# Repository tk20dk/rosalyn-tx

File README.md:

# rosalyn-tx
LoRa TX module for TURNIGY 9x

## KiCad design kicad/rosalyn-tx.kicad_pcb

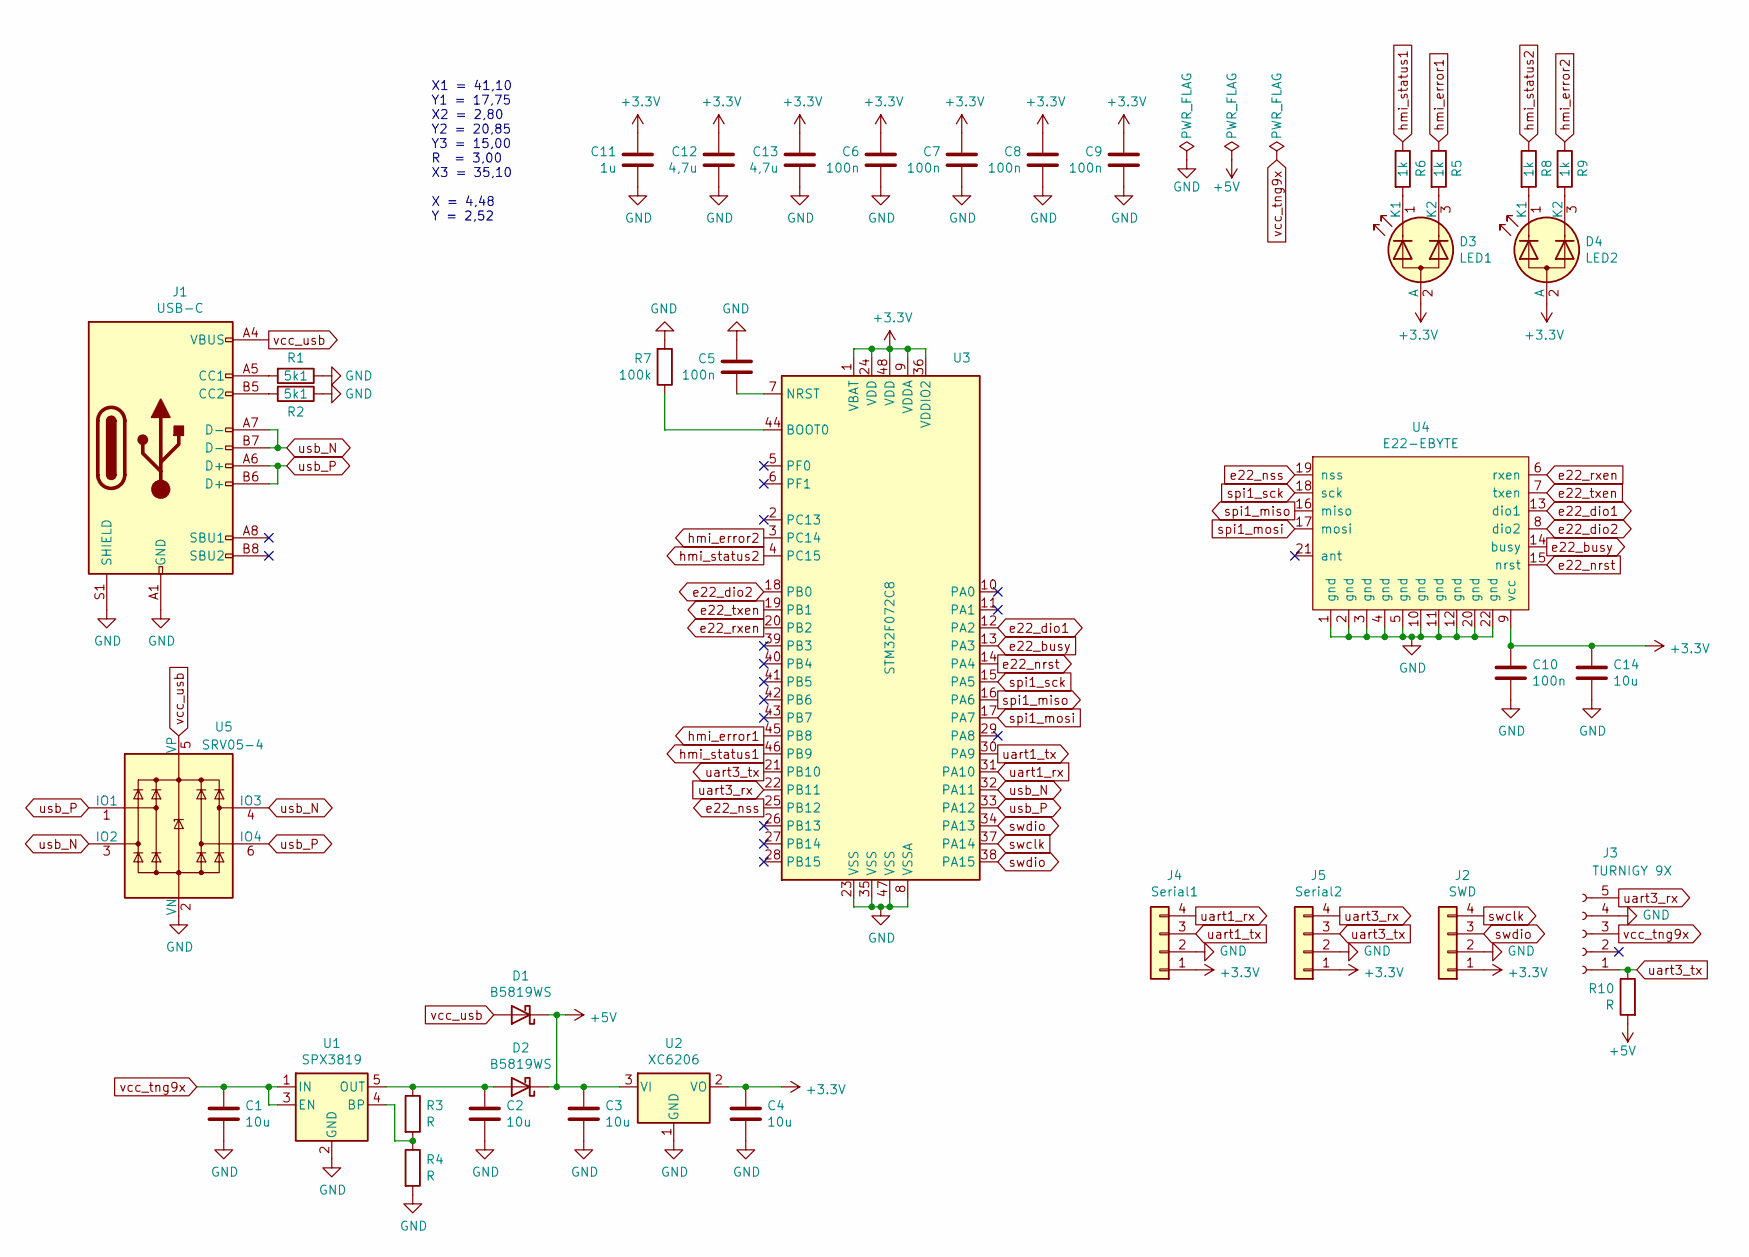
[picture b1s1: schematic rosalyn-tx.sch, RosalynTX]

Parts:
C1, C2, C14: 10u; C_0805_2012Metric
C3, C4: 10u; C_1206_3216Metric
C5, C6, C7, C8, C9, C10: 100n; C_0603_1608Metric
C11: 1u; C_0603_1608Metric
C12, C13: 4,7u; C_0603_1608Metric
D1, D2: B5819WS; D_SOD-323
D3: LED1; LED_D3.0mm-3
D4: LED2; LED_D3.0mm-3
J1: USB-C; usb-c_14pin_tht_vertical
J2: SWD; JST_SH_BM04B-SRSS-TB_1x04-1MP_P1.00mm_Vertical
J3: TURNIGY 9X; PinSocket_1x05_P2.54mm_Vertical
J4: Serial1; JST_SH_BM04B-SRSS-TB_1x04-1MP_P1.00mm_Vertical
J5: Serial2; JST_SH_BM04B-SRSS-TB_1x04-1MP_P1.00mm_Vertical
R1, R2: 5k1; R_0603_1608Metric
R3, R4, R10: R; R_0603_1608Metric
R5, R6, R8, R9: 1k; R_0603_1608Metric
R7: 100k; R_0603_1608Metric
U1: SPX3819; SOT-23-5
U2: XC6206; SOT-23
U3: STM32F072C8; LQFP-48_7x7mm_P0.5mm
U4: E22-EBYTE
U5: SRV05-4; SOT-23-6

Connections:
+3V3: C4.1, C6.2, C7.2, C8.2, C9.2, C10.1, C11.2, C12.2, C13.2, C14.1, D3.2 (A), D4.2 (A), J2.1, J4.1, J5.1, U2.2 (VO), U3.1 (VBAT), U3.9 (VDDA), U3.24 (VDD), U3.36 (VDDIO2), U3.48 (VDD), U4.9 (vcc)
+5V: C3.1, D1.1 (K), D2.1 (K), R10.2, U2.3 (VI)
unnamed: C2.1, D2.2 (A), R3.1, U1.5 (OUT)
unnamed: C5.1, U3.7 (NRST)
unnamed: D3.1 (K1), R6.2
unnamed: D3.3 (K2), R5.2
unnamed: D4.1 (K1), R8.2
unnamed: D4.3 (K2), R9.2
unnamed: J1.A5 (CC1), R1.2
unnamed: J1.B5 (CC2), R2.2
unnamed: R3.2, R4.1, U1.4 (BP)
unnamed: R7.1, U3.44 (BOOT0)
hmi_error: R5.1, U3.45 (PB8)
hmi_error_ext: R9.1, U3.3 (PC14)
hmi_status: R6.1, U3.46 (PB9)
hmi_status_ext: R8.1, U3.4 (PC15)
radio_busy: U3.13 (PA3), U4.14 (busy)
radio_dio1: U3.12 (PA2), U4.13 (dio1)
radio_dio2: U3.18 (PB0), U4.8 (dio2)
radio_nrst: U3.14 (PA4), U4.15 (nrst)
radio_nss: U3.25 (PB12), U4.19 (nss)
radio_rxen: U3.20 (PB2), U4.6 (rxen)
radio_txen: U3.19 (PB1), U4.7 (txen)
spi1_miso: U3.16 (PA6), U4.16 (miso)
spi1_mosi: U3.17 (PA7), U4.17 (mosi)
spi1_sck: U3.15 (PA5), U4.18 (sck)
swclk: J2.4, U3.37 (PA14)
swdio: J2.3, U3.34 (PA13), U3.38 (PA15)
uart1_rx: J4.4, U3.31 (PA10)
uart1_tx: J4.3, U3.30 (PA9)
uart3_rx: J3.5, J5.4, U3.22 (PB11)
uart3_tx: J3.1, J5.3, R10.1, U3.21 (PB10)
usb_N: J1.A7 (D-), J1.B7 (D-), U3.32 (PA11), U5.3 (IO2), U5.4 (IO3)
usb_P: J1.A6 (D+), J1.B6 (D+), U3.33 (PA12), U5.1 (IO1), U5.6 (IO4)
vcc_tng9x: C1.1, J3.3, U1.1 (IN), U1.3 (EN)
vcc_usb: D1.2 (A), J1.A4 (VBUS), J1.A9 (VBUS), J1.B4 (VBUS), J1.B9 (VBUS), U5.5 (VP)

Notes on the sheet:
X1 = 41,10 Y1 = 17,75 X2 = 2,80 Y2 = 20,85 Y3 = 15,00 R = 3,00 X3 = 35,10 X = 4,48 Y = 2,52

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
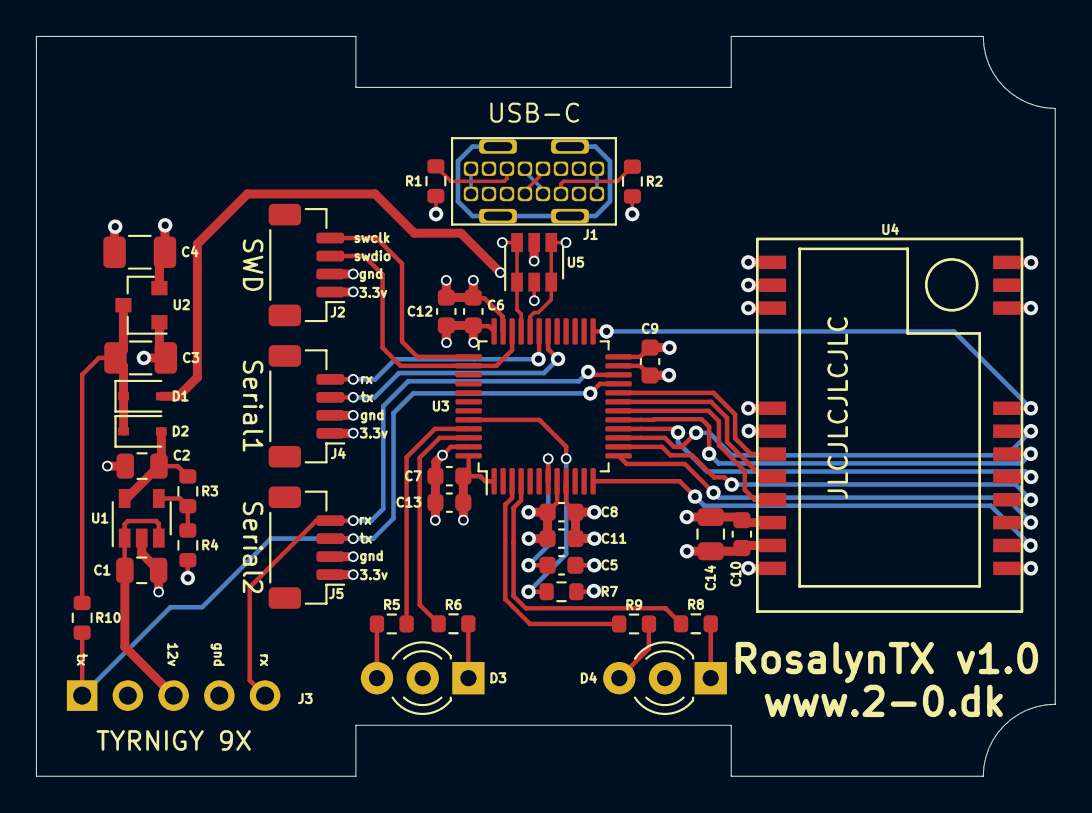
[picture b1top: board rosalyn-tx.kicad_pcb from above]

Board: 4 copper layers, 56.6 x 41.1 mm, 38 parts (1 on the bottom side), 37 nets.

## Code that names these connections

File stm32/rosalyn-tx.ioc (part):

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Mcu.Name=STM32F072C(8-B)Tx
Mcu.Package=LQFP48
Mcu.UserName=STM32F072C8Tx
PA10.GPIOParameters=GPIO_PuPd
PA10.GPIO_PuPd=GPIO_PULLUP
PA10.Mode=Asynchronous
PA10.Signal=USART1_RX
PA11.Mode=Device
PA11.Signal=USB_DM
PA12.Mode=Device
PA12.Signal=USB_DP
PA13.Mode=Serial_Wire
PA13.Signal=SYS_SWDIO
PA14.Mode=Serial_Wire
PA14.Signal=SYS_SWCLK
PA2.GPIOParameters=GPIO_Label
PA2.GPIO_Label=RADIO_DIO1
PA2.Signal=GPXTI2
PA3.GPIOParameters=GPIO_Label
PA3.GPIO_Label=RADIO_BUSY
PA3.Signal=GPIO_Input
PA4.GPIOParameters=PinState,GPIO_Label
PA4.GPIO_Label=RADIO_NRST
PA4.PinState=GPIO_PIN_SET
PA4.Signal=GPIO_Output
PA5.Mode=Full_Duplex_Master
PA5.Signal=SPI1_SCK
PA6.GPIOParameters=GPIO_PuPd
PA6.GPIO_PuPd=GPIO_PULLUP
PA6.Mode=Full_Duplex_Master
PA6.Signal=SPI1_MISO
PA7.Mode=Full_Duplex_Master
PA7.Signal=SPI1_MOSI
PA9.Mode=Asynchronous
PA9.Signal=USART1_TX
PB0.GPIOParameters=GPIO_Label
PB0.GPIO_Label=RADIO_DIO2
PB0.Signal=GPIO_Input
PB1.GPIOParameters=GPIO_Label
PB1.GPIO_Label=RADIO_TXEN
PB1.Signal=GPIO_Output
PB11.GPIOParameters=GPIO_ModeDefaultPP
PB11.GPIO_ModeDefaultPP=GPIO_MODE_AF_PP
PB11.Signal=S_TIM2_CH4
PB12.GPIOParameters=PinState,GPIO_Label
PB12.GPIO_Label=RADIO_NSS
PB12.PinState=GPIO_PIN_SET
PB12.Signal=GPIO_Output
PB2.GPIOParameters=GPIO_Label
PB2.GPIO_Label=RADIO_RXEN
PB2.Signal=GPIO_Output
PB8.GPIOParameters=PinState,GPIO_Label
PB8.GPIO_Label=HMI_ERROR
PB8.PinState=GPIO_PIN_SET
PB8.Signal=GPIO_Output
PB9.GPIOParameters=PinState,GPIO_Label
PB9.GPIO_Label=HMI_STATUS
PB9.PinState=GPIO_PIN_SET
PB9.Signal=GPIO_Output
PC14-OSC32_IN.GPIOParameters=PinState,GPIO_Label
PC14-OSC32_IN.GPIO_Label=HMI_ERROR_EXT
PC14-OSC32_IN.PinState=GPIO_PIN_SET
PC14-OSC32_IN.Signal=GPIO_Output
PC15-OSC32_OUT.GPIOParameters=PinState,GPIO_Label
PC15-OSC32_OUT.GPIO_Label=HMI_STATUS_EXT
PC15-OSC32_OUT.PinState=GPIO_PIN_SET
PC15-OSC32_OUT.Signal=GPIO_Output
RCC.SYSCLKFreq_VALUE=48000000
RCC.SYSCLKSource=RCC_SYSCLKSOURCE_HSI48
board=custom

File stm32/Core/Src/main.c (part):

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
  LL_AHB1_GRP1_EnableClock(LL_AHB1_GRP1_PERIPH_GPIOA);
  /**USART1 GPIO Configuration
  PA9   ------> USART1_TX
  PA10   ------> USART1_RX
  */
  GPIO_InitStruct.Pin = LL_GPIO_PIN_9;
  GPIO_InitStruct.Mode = LL_GPIO_MODE_ALTERNATE;
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  __HAL_RCC_GPIOB_CLK_ENABLE();

  /*Configure GPIO pin Output Level */
  HAL_GPIO_WritePin(GPIOC, HMI_ERROR_EXT_Pin|HMI_STATUS_EXT_Pin, GPIO_PIN_SET);

  /*Configure GPIO pin Output Level */
  HAL_GPIO_WritePin(RADIO_NRST_GPIO_Port, RADIO_NRST_Pin, GPIO_PIN_SET);

  /*Configure GPIO pin Output Level */
  HAL_GPIO_WritePin(GPIOB, RADIO_TXEN_Pin|RADIO_RXEN_Pin, GPIO_PIN_RESET);

  /*Configure GPIO pin Output Level */
  HAL_GPIO_WritePin(GPIOB, RADIO_NSS_Pin|HMI_ERROR_Pin|HMI_STATUS_Pin, GPIO_PIN_SET);

  /*Configure GPIO pin : PC13 */
  GPIO_InitStruct.Pin = GPIO_PIN_13;
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  GPIO_InitStruct.Pull = GPIO_NOPULL;
  HAL_GPIO_Init(GPIOC, &GPIO_InitStruct);

  /*Configure GPIO pins : HMI_ERROR_EXT_Pin HMI_STATUS_EXT_Pin */
  GPIO_InitStruct.Pin = HMI_ERROR_EXT_Pin|HMI_STATUS_EXT_Pin;
  GPIO_InitStruct.Mode = GPIO_MODE_OUTPUT_PP;
  GPIO_InitStruct.Pull = GPIO_NOPULL;
  GPIO_InitStruct.Speed = GPIO_SPEED_FREQ_LOW;
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  GPIO_InitStruct.Pull = GPIO_NOPULL;
  HAL_GPIO_Init(GPIOF, &GPIO_InitStruct);

  /*Configure GPIO pins : PA0 PA1 PA8 PA15 */
  GPIO_InitStruct.Pin = GPIO_PIN_0|GPIO_PIN_1|GPIO_PIN_8|GPIO_PIN_15;
  GPIO_InitStruct.Mode = GPIO_MODE_ANALOG;
  GPIO_InitStruct.Pull = GPIO_NOPULL;
  HAL_GPIO_Init(GPIOA, &GPIO_InitStruct);

  /*Configure GPIO pin : RADIO_DIO1_Pin */
  GPIO_InitStruct.Pin = RADIO_DIO1_Pin;
  GPIO_InitStruct.Mode = GPIO_MODE_IT_RISING;
  GPIO_InitStruct.Pull = GPIO_NOPULL;
  HAL_GPIO_Init(RADIO_DIO1_GPIO_Port, &GPIO_InitStruct);

  /*Configure GPIO pin : RADIO_BUSY_Pin */
  GPIO_InitStruct.Pin = RADIO_BUSY_Pin;
  GPIO_InitStruct.Mode = GPIO_MODE_INPUT;
  GPIO_InitStruct.Pull = GPIO_NOPULL;
  HAL_GPIO_Init(RADIO_BUSY_GPIO_Port, &GPIO_InitStruct);

  /*Configure GPIO pin : RADIO_NRST_Pin */
  GPIO_InitStruct.Pin = RADIO_NRST_Pin;
  GPIO_InitStruct.Mode = GPIO_MODE_OUTPUT_PP;
  GPIO_InitStruct.Pull = GPIO_NOPULL;
  GPIO_InitStruct.Speed = GPIO_SPEED_FREQ_LOW;
  HAL_GPIO_Init(RADIO_NRST_GPIO_Port, &GPIO_InitStruct);

  /*Configure GPIO pin : RADIO_DIO2_Pin */
  GPIO_InitStruct.Pin = RADIO_DIO2_Pin;
  GPIO_InitStruct.Mode = GPIO_MODE_INPUT;
  GPIO_InitStruct.Pull = GPIO_NOPULL;
  HAL_GPIO_Init(RADIO_DIO2_GPIO_Port, &GPIO_InitStruct);

  /*Configure GPIO pins : RADIO_TXEN_Pin RADIO_RXEN_Pin RADIO_NSS_Pin HMI_ERROR_Pin
                           HMI_STATUS_Pin */
  GPIO_InitStruct.Pin = RADIO_TXEN_Pin|RADIO_RXEN_Pin|RADIO_NSS_Pin|HMI_ERROR_Pin
                          |HMI_STATUS_Pin;
  GPIO_InitStruct.Mode = GPIO_MODE_OUTPUT_PP;
  GPIO_InitStruct.Pull = GPIO_NOPULL;
  GPIO_InitStruct.Speed = GPIO_SPEED_FREQ_LOW;
  HAL_GPIO_Init(GPIOB, &GPIO_InitStruct);

  /*Configure GPIO pins : PB10 PB13 PB14 PB15
                           PB3 PB4 PB5 PB6
                           PB7 */
  GPIO_InitStruct.Pin = GPIO_PIN_10|GPIO_PIN_13|GPIO_PIN_14|GPIO_PIN_15
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
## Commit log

2020-11-19 created initial kicad and stm32 projects
2020-11-23 rosalyn-tx v1.0
2020-11-25 added ppm decoder
2020-11-26 added TIM2 IC3
2020-11-26 added Sx1268 driver
2020-11-26 added schematic with new radio port names
2020-11-26 added led drivers
2020-11-26 added nvdata driver
2020-11-26 updated nvdata driver
2020-12-12 ppm to transmit is working
2020-12-13 removed crypto files
2020-12-13 fixed duplicated definition of MIN/MAX macro
2020-12-13 enabled CRC to make AES work
2020-12-15 enabled TXCO to remove startup delay

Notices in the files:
stm32/Core/Src/main.c:
© Copyright (c) 2020 STMicroelectronics.
All rights reserved.
This software component is licensed by ST under BSD 3-Clause license,
the "License"; You may not use this file except in compliance with the
License. You may obtain a copy of the License at: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
(C) COPYRIGHT STMicroelectronics *****END OF FILE
